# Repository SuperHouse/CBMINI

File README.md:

Chair Control Breakout Mini
===========================

Connects between an electric wheelchair input device and the chair
controller, so that the input device can be read by an Arduino and
redirected to another system.

The output can be isolated so that the chair won't receive the input
signals, preventing it from moving while the input is being used for
another purpose such as controlling a computer or remote control
device.

The breakout can send the output to either a connected USB host such
as a computer, or other devices via CAN bus so the wheelchair controls
can be used to fly a drone or drive a remote control car.

Features:

 * 1 x input device connection.
 * 1 x input device pass-through output
 * CAN bus
 * Can derives 12V power from the host wheelchair controller or separately

More information is available at:

  http://www.superhouse.tv/cbmini

Hardware
--------
The "Hardware" directory contains the PCB design as an EAGLE project.
EAGLE PCB design software is available from Autodesk free for
non-commercial use.

Firmware
--------
The "Firmware" directory contains example firmware as an Arduino
project.

Credits
-------
Jonathan Oxer jon@oxer.com.au

License
-------
Copyright 2017-2020 SuperHouse Automation Pty Ltd  www.superhouse.tv  

The hardware portion of this project is licensed under the TAPR Open
Hardware License (www.tapr.org/OHL). The "license" folder within this
repository contains a copy of this license in plain text format.

The software portion of this project is licensed under the Simplified
BSD License. The "licence" folder within this project contains a
copy of this license in plain text format.

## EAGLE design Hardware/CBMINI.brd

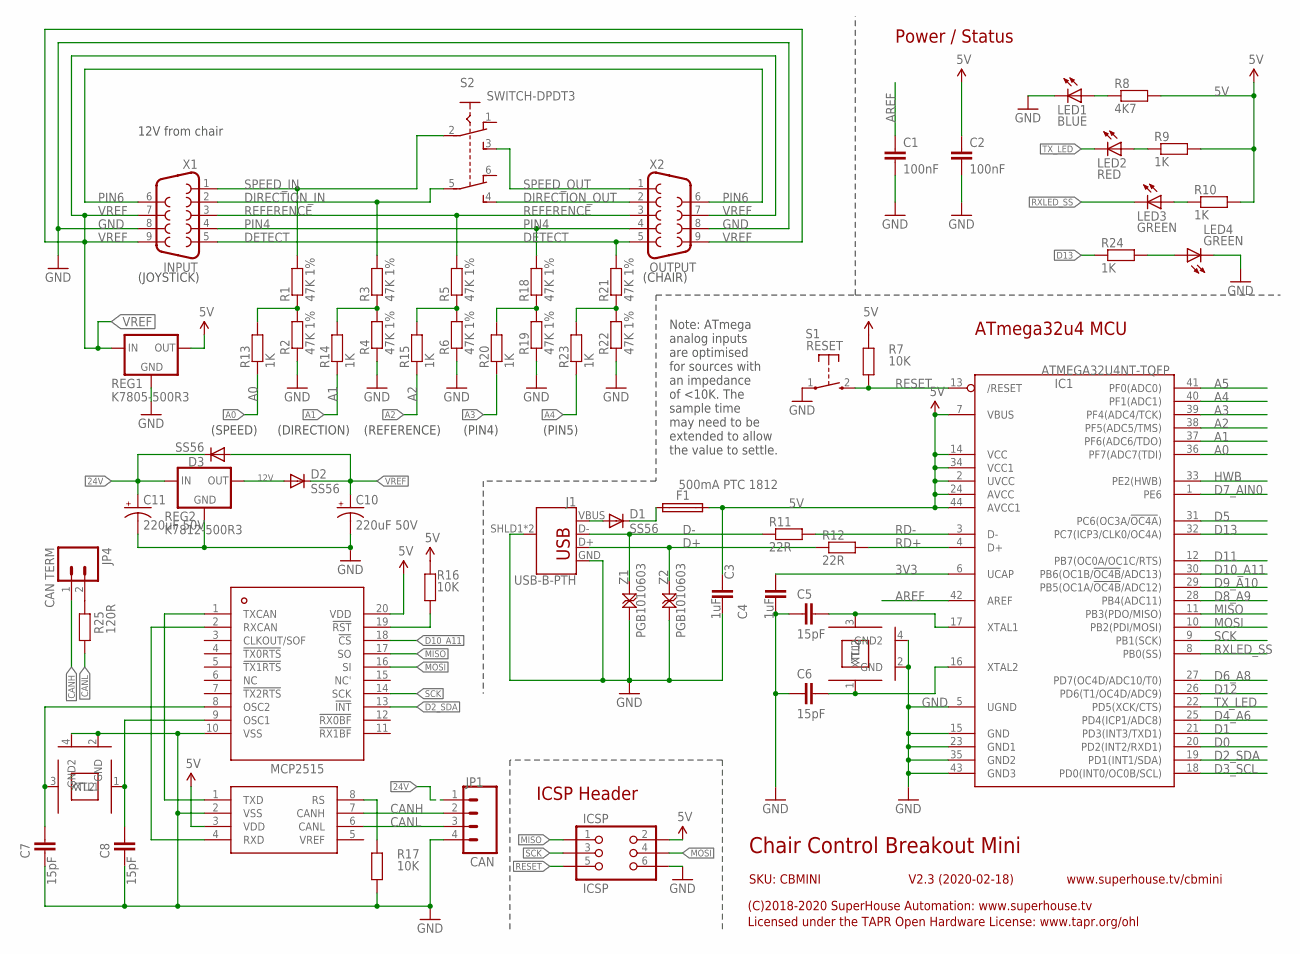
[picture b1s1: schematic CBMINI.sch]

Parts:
C1, C2: 100nF; C0603
C3, C4: 1uF; C0603
C5, C6, C7, C8: 15pF; C0603
C10, C11: 220uF 50V; PANASONIC_G
D1, D2, D3: SS56; SMA-DIODE
F1: 500mA PTC 1812; 1812
IC1: ATMEGA32U4NT-TQFP; TQFP44
IC2: MCP2515; TSSOP20
IC3: MCP2551; SO08
ICSP: ICSP; 2X03-ICSP
J1: USB-B-PTH
JP1: CAN; 1X04-P
JP4: CAN TERM; 1X02-P
LED1: BLUE; LED-0603
LED2: RED; LED-0603
LED3, LED4: GREEN; LED-0603
R1, R2, R3, R4, R5, R6, R18, R19, R21, R22: 47K 1%; R0603
R7, R16, R17: 10K; R0603
R8: 4K7; R0603
R9, R10, R13, R14, R15, R20, R23, R24: 1K; R0603
R11, R12: 22R; R0603
R25: 120R; R0603
REG1: K7805-500R3; K78XX-500R3
REG2: K7812-500R3; K78XX-500R3
S1: RESET; TACTILE_SMT_3X4X2
S2: SWITCH-DPDT3; 7201SD9AV2BE
X1: INPUT; DB9-PCB-PLUG
X2: OUTPUT; DB9-PCB-SOCKET
XTL1, XTL2: 16MHz; CRYSTAL-SMD-3X2
Z1, Z2: PGB1010603; TVS0603

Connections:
3V3: C4.2, IC1.6 (UCAP)
5V: C2.1, C3.1, F1.2, IC1.2 (UVCC), IC1.7 (VBUS), IC1.14 (VCC), IC1.24 (AVCC), IC1.34 (VCC1), IC1.44 (AVCC1), IC2.20 (VDD), IC3.3 (VDD), ICSP.2, R7.2, R8.2, R9.2, R10.2, R16.2, REG1.3 (OUT)
12V: D2.A, REG2.3 (OUT)
24V: C11.+, D3.C, JP1.1, REG2.1 (IN)
A0: IC1.36 (PF7(ADC7(TDI)), R13.1
A1: IC1.37 (PF6(ADC6/TDO)), R14.1
A2: IC1.38 (PF5(ADC5/TMS)), R15.1
A3: IC1.39 (PF4(ADC4/TCK)), R20.1
A4: IC1.40 (PF1(ADC1)), R23.1
A5: IC1.41 (PF0(ADC0))
AREF: C1.1, IC1.42 (AREF)
CANH: IC3.7 (CANH), JP1.2, JP4.1
CANL: IC3.6 (CANL), JP1.3, R25.1
D0: IC1.20 (PD2(INT2/RXD1))
D1: IC1.21 (PD3(INT3/TXD1))
D2_SDA: IC1.19 (PD1(INT1/SDA)), IC2.13 (!INT)
D3_SCL: IC1.18 (PD0(INT0/OC0B/SCL))
D4_A6: IC1.25 (PD4(ICP1/ADC8))
D5: IC1.31 (PC6(OC3A/!OC4A!))
D6_A8: IC1.27 (PD7(OC4D/ADC10/T0))
D7_AIN0: IC1.1 (PE6)
D8_A9: IC1.28 (PB4(ADC11))
D9_A10: IC1.29 (PB5(OC1A/!OC4B!/ADC12))
D10_A11: IC1.30 (PB6(OC1B/!OC4B!/ADC13)), IC2.18 (!CS)
D11: IC1.12 (PB7(OC0A/OC1C/RTS))
D12: IC1.26 (PD6(T1/OC4D/ADC9))
D13: IC1.32 (PC7(ICP3/CLK0/OC4A)), R24.1
D+: J1.D+, R12.1, Z2.2
D-: J1.D-, R11.1, Z1.2
DETECT: R21.2, X1.5, X2.5
DIRECTION_IN: R3.2, S2.5, X1.2
DIRECTION_OUT: S2.4, X2.2
GND: C1.2, C2.2, C3.2, C4.1, C5.1, C6.1, C7.1, C8.1, C10.-, C11.-, IC1.5 (UGND), IC1.15 (GND), IC1.23 (GND1), IC1.35 (GND2), IC1.43 (GND3), IC2.10 (VSS), IC3.2 (VSS), ICSP.6, J1.GND, J1.SHLD1 (SHIELD), J1.SHLD2 (SHIELD), JP1.4, LED1.C, LED4.C, R2.1, R4.1, R6.1, R17.1, R19.1, R22.1, REG1.2 (GND), REG2.2 (GND), S1.1, X1.8, X2.8, XTL1.2 (GND), XTL1.4 (GND2), XTL2.2 (GND), XTL2.4 (GND2), Z1.1, Z2.1
HWB: IC1.33 (PE2(HWB))
MISO: IC1.11 (PB3(PDO/MISO)), IC2.17 (SO), ICSP.1
MOSI: IC1.10 (PB2(PDI/MOSI)), IC2.16 (SI), ICSP.4
unnamed: LED4.A, R24.2
unnamed: R1.1, R2.2, R13.2
unnamed: R3.1, R4.2, R14.2
unnamed: R5.1, R6.2, R15.2
unnamed: LED1.A, R8.1
unnamed: LED2.A, R9.1
unnamed: LED3.A, R10.1
unnamed: IC2.1 (TXCAN), IC3.1 (TXD)
unnamed: IC2.19 (!RST), R16.1
unnamed: C5.2, IC1.17 (XTAL1), XTL1.3 (XTL2)
unnamed: C6.2, IC1.16 (XTAL2), XTL1.1 (XTL1)
unnamed: IC2.2 (RXCAN), IC3.4 (RXD)
unnamed: C8.2, IC2.9 (OSC1), XTL2.1 (XTL1)
unnamed: IC3.8 (RS), R17.2
unnamed: D1.C, F1.1
unnamed: C7.2, IC2.8 (OSC2), XTL2.3 (XTL2)
unnamed: R18.1, R19.2, R20.2
unnamed: JP4.2, R25.2
unnamed: R21.1, R22.2, R23.2
PIN4: R18.2, X1.4, X2.4
PIN6: X1.6, X2.6
RD+: IC1.4 (D+), R12.2
RD-: IC1.3 (D-), R11.2
REFERENCE: R5.2, X1.3, X2.3
RESET: IC1.13 (/RESET), ICSP.5, R7.1, S1.2 (S)
RXLED_SS: IC1.8 (PB0(SS)), LED3.C
SCK: IC1.9 (PB1(SCK)), IC2.14 (SCK), ICSP.3
SPEED_IN: R1.2, S2.2, X1.1
SPEED_OUT: S2.3, X2.1
TX_LED: IC1.22 (PD5(XCK/CTS)), LED2.C
USB+: D1.A, J1.VBUS
VREF: C10.+, D2.C, D3.A, REG1.1 (IN), X1.7, X1.9, X2.7, X2.9

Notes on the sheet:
(JOYSTICK)
(CHAIR)
Note: ATmega analog inputs are optimised for sources with an impedance of <10K. The sample time may need to be extended to allow the value to settle.
(SPEED)
(DIRECTION)
(REFERENCE)
ICSP Header
ATmega32u4 MCU
Chair Control Breakout Mini
V2.3 (2020-02-18)
SKU: CBMINI
(C)2018-2020 SuperHouse Automation: www.superhouse.tv
Licensed under the TAPR Open Hardware License: www.tapr.org/ohl
www.superhouse.tv/cbmini
Power / Status
12V from chair
(PIN4)
(PIN5)

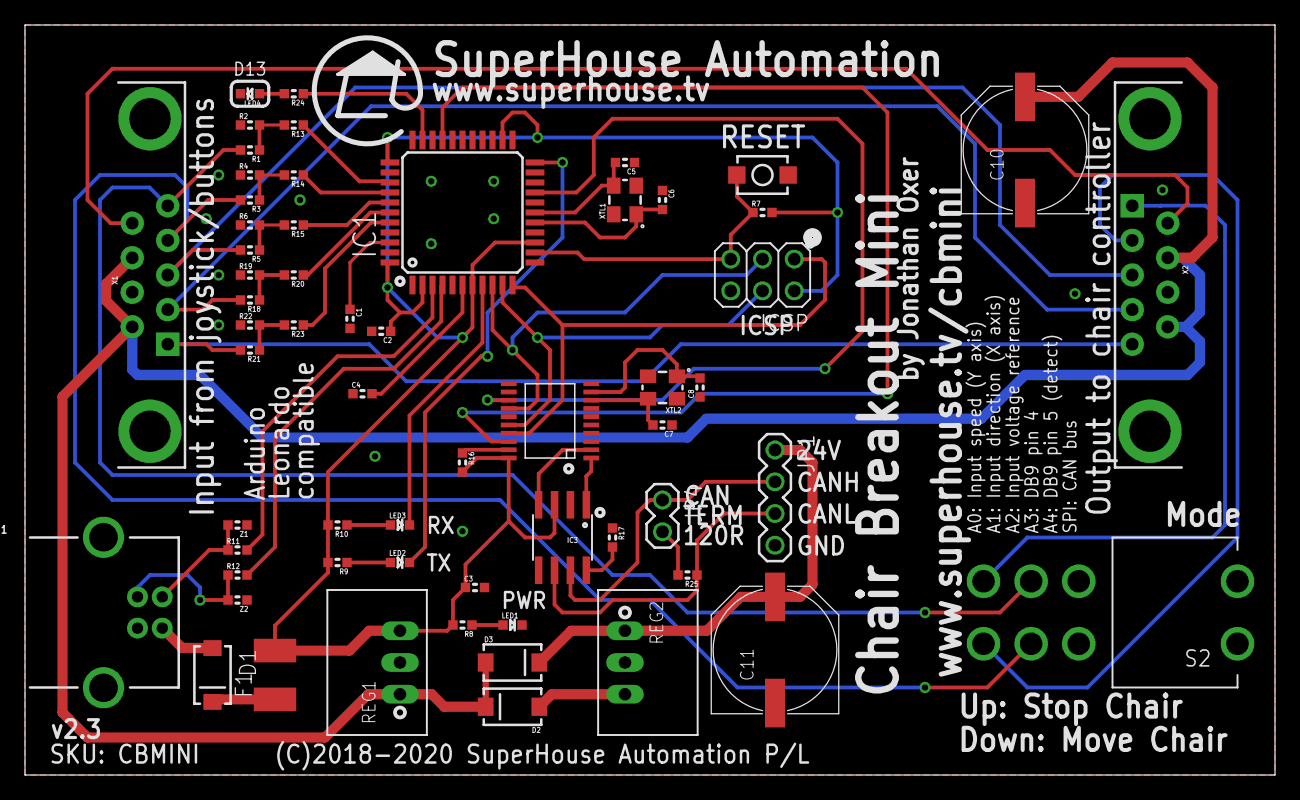
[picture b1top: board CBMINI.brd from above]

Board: 2 copper layers, 100.0 x 60.0 mm, 60 parts (0 on the bottom side), 55 nets.

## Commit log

2020-03-17 Isolation diodes between CAN and chair power, and switched parts to SuperHouse libraries for v2.3 release
2020-07-14 Start of major project restructure to merge everything together
2020-07-14 Merged firmware
2020-07-14 Added images
2020-07-14 Major firmware update

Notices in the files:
Hardware/CBMINI.brd:
(C)2018-2020 SuperHouse Automation P/L
